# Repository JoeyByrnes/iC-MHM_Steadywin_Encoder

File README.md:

# iC-MHM_Steadywin_Encoder
PCB Design Files for iC-MHM Based Encoder PCB for the Steadywin v3 Motor

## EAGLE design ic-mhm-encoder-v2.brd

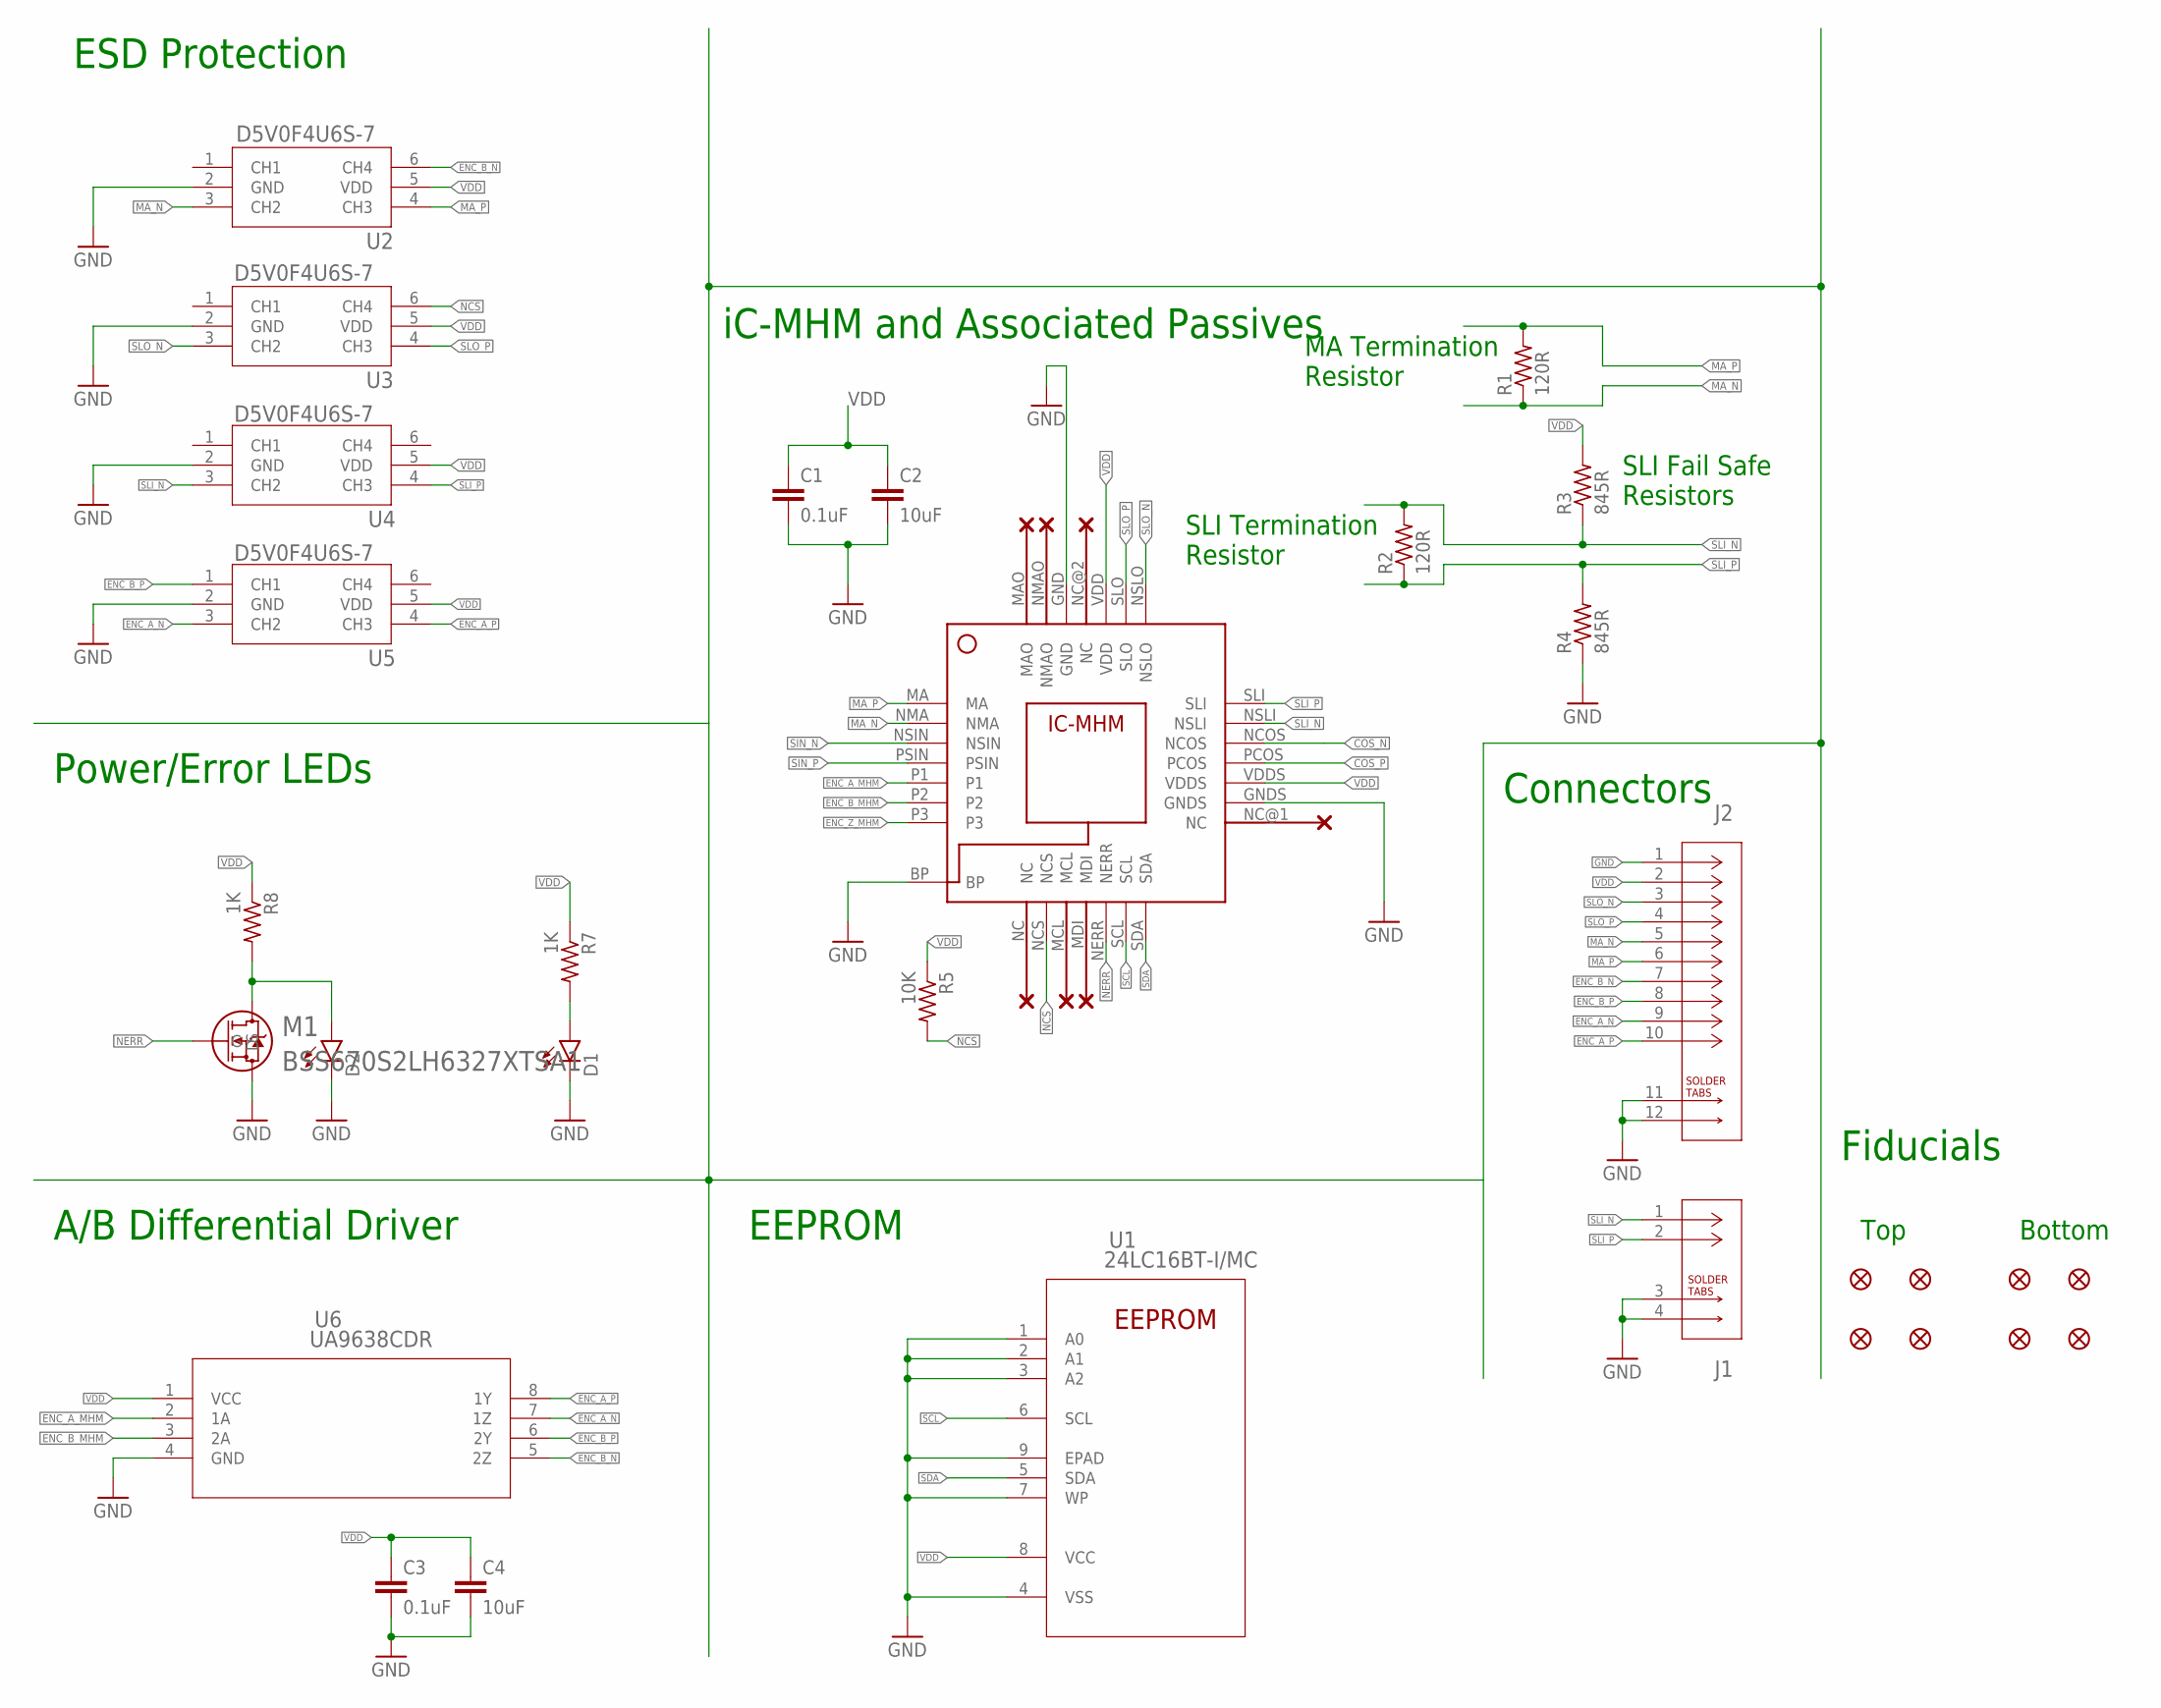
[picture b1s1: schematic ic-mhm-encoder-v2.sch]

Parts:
C1, C3: 0.1uF; C0603
C2, C4: 10uF; C0603
D1, D2: LEDSML0603; SML0603
FID1, FID2, FID3, FID4, FID5, FID6, FID7, FID8: FIDUCIAL_1MM
J1: 2023960207; CON_2023960207
J2: 2023961007; CON_2023961007
M1: BSS670S2LH6327XTSA1; PG-SOT23-3-5_INF
R1, R2: 120R; R0603
R3, R4: 845R; R0603
R5: 10K; R0603
R7, R8: 1K; R0603
U1: 24LC16BT-I/MC; DFN8_2X3MC_MCH
U2, U3, U4, U5: D5V0F4U6S-7; SOT-363_DIO
U6: UA9638CDR; D8
U$1: IC-MHM

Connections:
COS_N: U$1.NCOS
COS_P: U$1.PCOS
ENC_A_MHM: U6.2 (1A), U$1.P1
ENC_A_N: J2.9, U5.3 (CH2), U6.7 (1Z)
ENC_A_P: J2.10, U5.4 (CH3), U6.8 (1Y)
ENC_B_MHM: U6.3 (2A), U$1.P2
ENC_B_N: J2.7, U2.6 (CH4), U6.5 (2Z)
ENC_B_P: J2.8, U5.1 (CH1), U6.6 (2Y)
ENC_Z_MHM: U$1.P3
GND: C1.2, C2.2, C3.2, C4.2, D1.C, D2.C, J1.3, J1.4, J2.1, J2.11, J2.12, M1.2 (S), R4.1, U1.1 (A0), U1.2 (A1), U1.3 (A2), U1.4 (VSS), U1.7 (WP), U1.9 (EPAD), U2.2 (GND), U3.2 (GND), U4.2 (GND), U5.2 (GND), U6.4 (GND), U$1.BP, U$1.GND, U$1.GNDS
MA_N: J2.5, R1.1, U2.3 (CH2), U$1.NMA
MA_P: J2.6, R1.2, U2.4 (CH3), U$1.MA
unnamed: D1.A, R7.2
unnamed: D2.A, M1.3 (D), R8.2
NCS: R5.2, U3.6 (CH4), U$1.NCS
NERR: M1.1 (G), U$1.NERR
SCL: U1.6 (SCL), U$1.SCL
SDA: U1.5 (SDA), U$1.SDA
SIN_N: U$1.NSIN
SIN_P: U$1.PSIN
SLI_N: J1.1, R2.2, R3.1, U4.3 (CH2), U$1.NSLI
SLI_P: J1.2, R2.1, R4.2, U4.4 (CH3), U$1.SLI
SLO_N: J2.3, U3.3 (CH2), U$1.NSLO
SLO_P: J2.4, U3.4 (CH3), U$1.SLO
VDD: C1.1, C2.1, C3.1, C4.1, J2.2, R3.2, R5.1, R7.1, R8.1, U1.8 (VCC), U2.5 (VDD), U3.5 (VDD), U4.5 (VDD), U5.5 (VDD), U6.1 (VCC), U$1.VDD, U$1.VDDS

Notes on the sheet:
MA Termination Resistor
SLI Termination Resistor
SLI Fail Safe Resistors
ESD Protection
iC-MHM and Associated Passives
Fiducials
Power/Error LEDs
A/B Differential Driver
EEPROM
Connectors
Top
Bottom

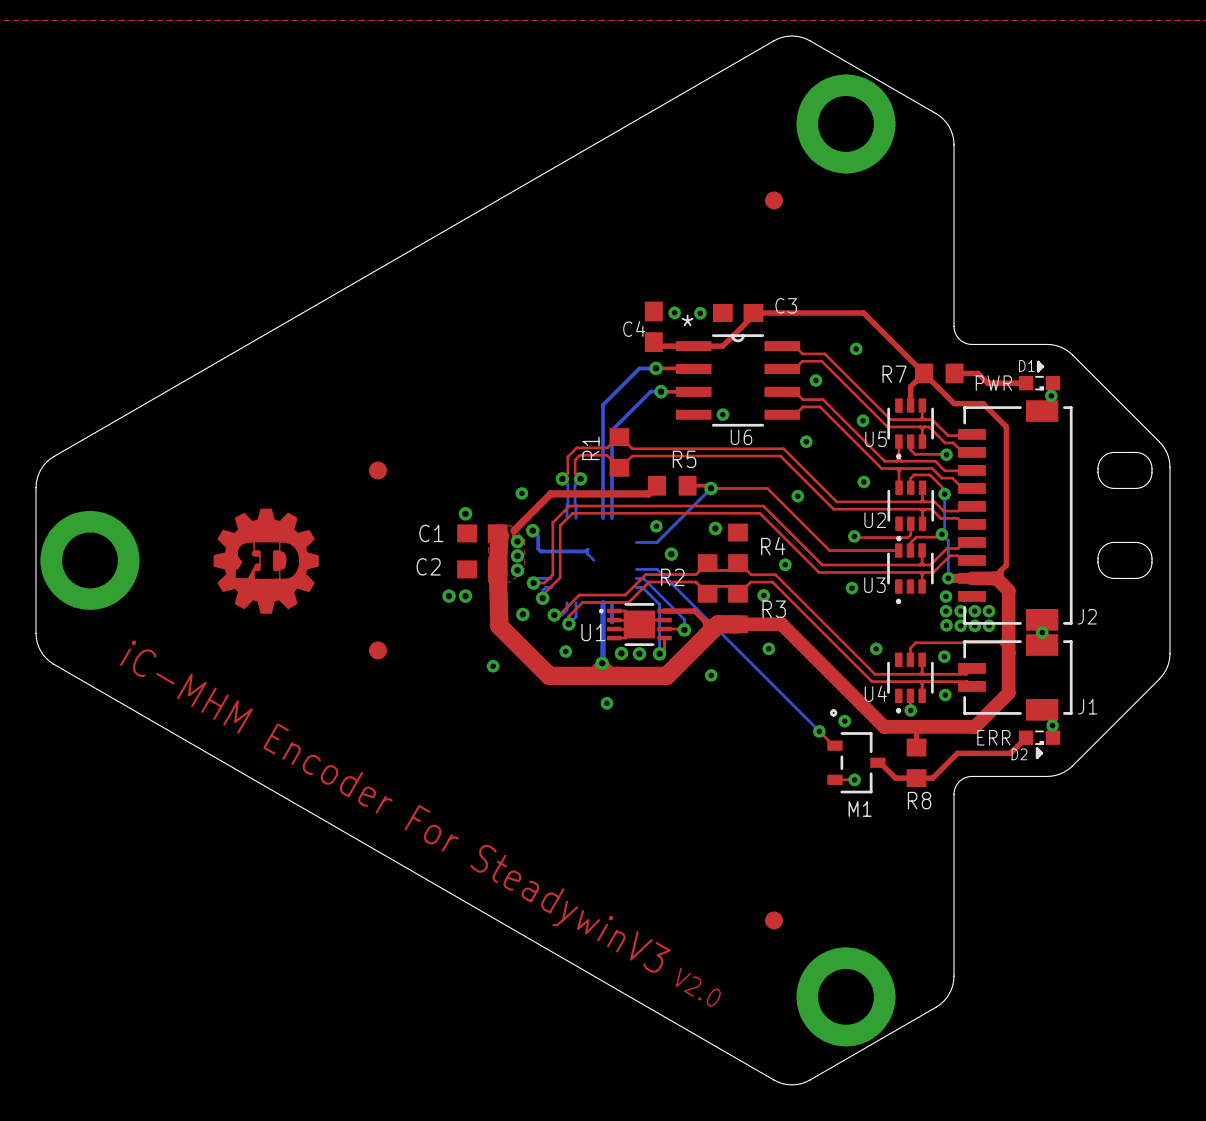
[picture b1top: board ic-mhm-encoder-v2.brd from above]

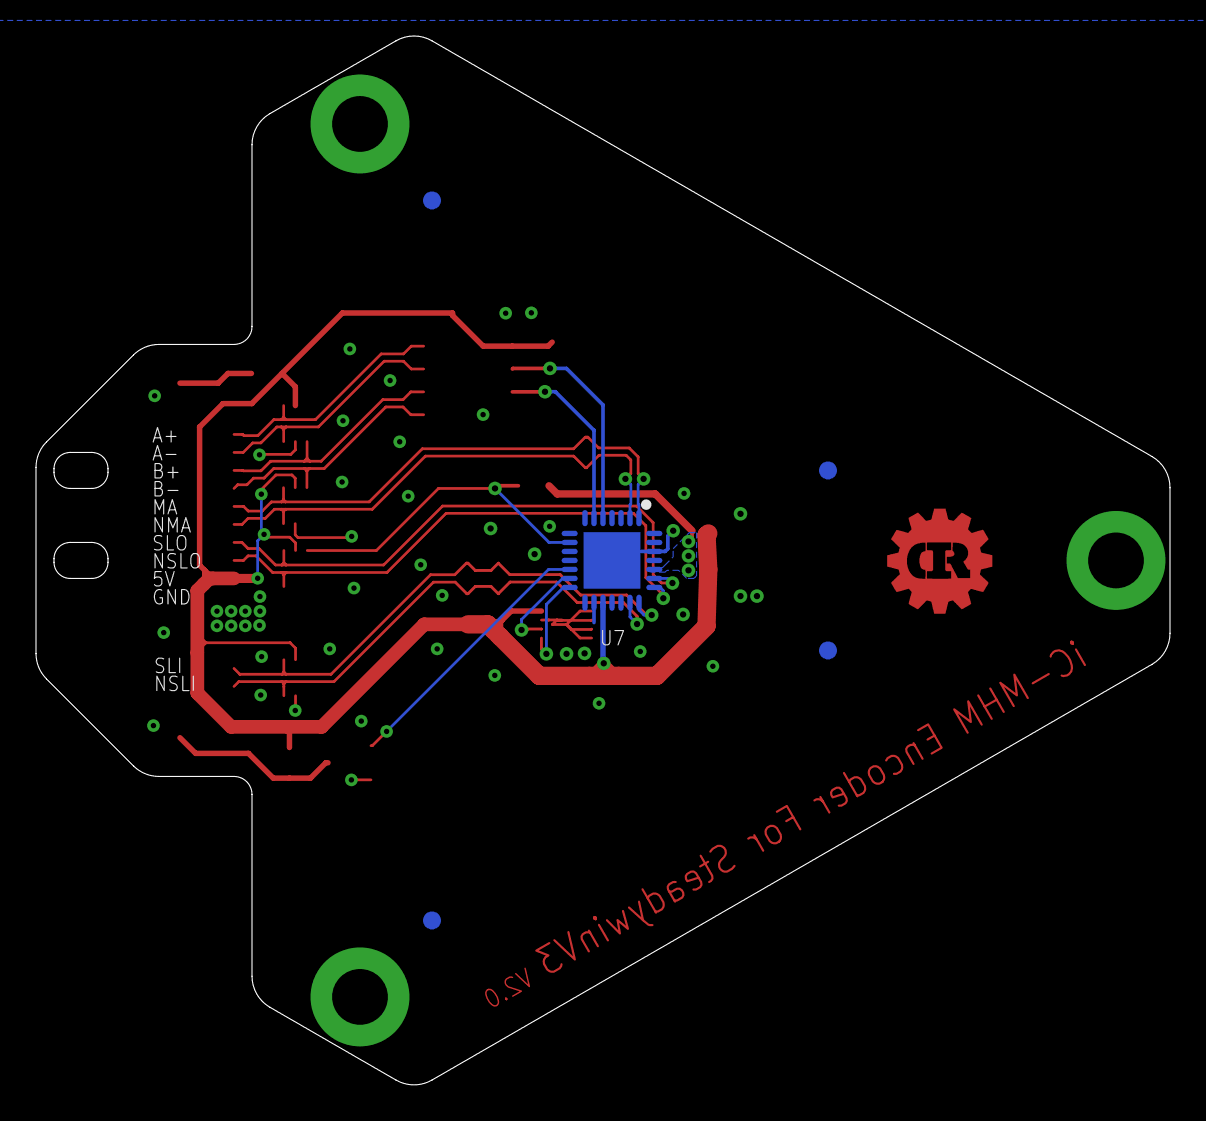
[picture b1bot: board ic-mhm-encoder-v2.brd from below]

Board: 4 copper layers, 63.0 x 58.3 mm, 31 parts (5 on the bottom side), 20 nets.

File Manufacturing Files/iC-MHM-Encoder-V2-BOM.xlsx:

Manufacturer Part Number | Manufacturer Name | Description | QTY | Digi-Key Part Number 1 | Datasheet | Reference Designator
24LC16BT-I/MC | Microchip Technology | IC EEPROM 16KBIT I2C 400KHZ 8DFN | 1 | 24LC16BT-I/MCCT-ND | https://ww1.microchip.com/downloads/en/DeviceDoc/20001703M.pdf | U1
BSS670S2LH6327XTSA1 | Infineon Technologies | MOSFET N-CH 55V 540MA SOT23-3 | 1 | BSS670S2LH6327XTSA1CT-ND | https://www.infineon.com/dgdl/BSS670S2L_Rev2.5.pdf?folderId=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 | M1
D5V0F4U6S-7 | Diodes Incorporated | TVS DIODE 5.5VWM 12VC SOT363 | 4 | 31-D5V0F4U6S-7CT-ND | https://www.diodes.com/assets/Datasheets/D5V0F4U6S.pdf | U2, U3, U4, U5
06035C104K4T4A | KYOCERA AVX | CAP CER 0.1UF 50V X7R 0603 | 2 | 478-9903-1-ND | https://datasheets.kyocera-avx.com/AutoMLCC.pdf | C1, C3
0603ZD106KAT2A | KYOCERA AVX | CAP CER 10UF 10V X5R 0603 | 2 | 478-10766-1-ND | https://datasheets.kyocera-avx.com/cx5r.pdf | C2, C4
ERJ-PA3F1200V | Panasonic Electronic Components | RES SMD 120 OHM 1% 1/3W 0603 | 2 | P120BYCT-ND | https://industrial.panasonic.com/cdbs/www-data/pdf/RDO0000/A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 | R1, R2
RE0603FRE071KL | YAGEO | RES SMD 1K OHM 1% 1/10W 0603 | 2 | 13-RE0603FRE071KLCT-ND | https://www.yageo.com/upload/media/product/productsearch/dat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 | R7, R8
ESR03EZPF1002 | Rohm Semiconductor | RES SMD 10K OHM 1% 1/4W 0603 | 1 | RHM10KADCT-ND | https://fscdn.rohm.com/en/products/databook/datasheet/passiv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 | R5
RC0603FR-07845RL | YAGEO | RES 845 OHM 1% 1/10W 0603 | 2 | 311-845HRCT-ND | https://www.yageo.com/upload/media/product/productsearch/dat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 | R3, R4
150060RS75000 | Würth Elektronik | LED RED CLEAR 0603 SMD | 1 | 732-4978-1-ND | https://www.we-online.com/katalog/datasheet/150060RS75000.pdf | D2
150060VS75000 | Würth Elektronik | LED GREEN CLEAR 0603 SMD | 1 | 732-4980-1-ND | https://www.we-online.com/katalog/datasheet/150060VS75000.pdf | D1
UA9638CDR | Texas Instruments | IC DRIVER 2/0 8SOIC | 1 | 296-15058-1-ND | https://www.ti.com/general/docs/suppproductinfo.tsp?distId=1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 | U6
2023960207 | Molex | CONN HEADER SMD R/A 2POS 1MM | 1 | WM26783CT-ND | https://www.molex.com/pdm_docs/sd/2023960207_sd.pdf | J1
2023961007 | Molex | CONN HEADER SMD R/A 10POS 1MM | 1 | WM26787CT-ND | https://www.molex.com/pdm_docs/sd/2023961007_sd.pdf | J2
iC-MHM | iC-Haus | https://www.ichaus.de/product/ic-mhm | 1 | N/A | https://www.ichaus.de/MHM_datasheet_en | U7

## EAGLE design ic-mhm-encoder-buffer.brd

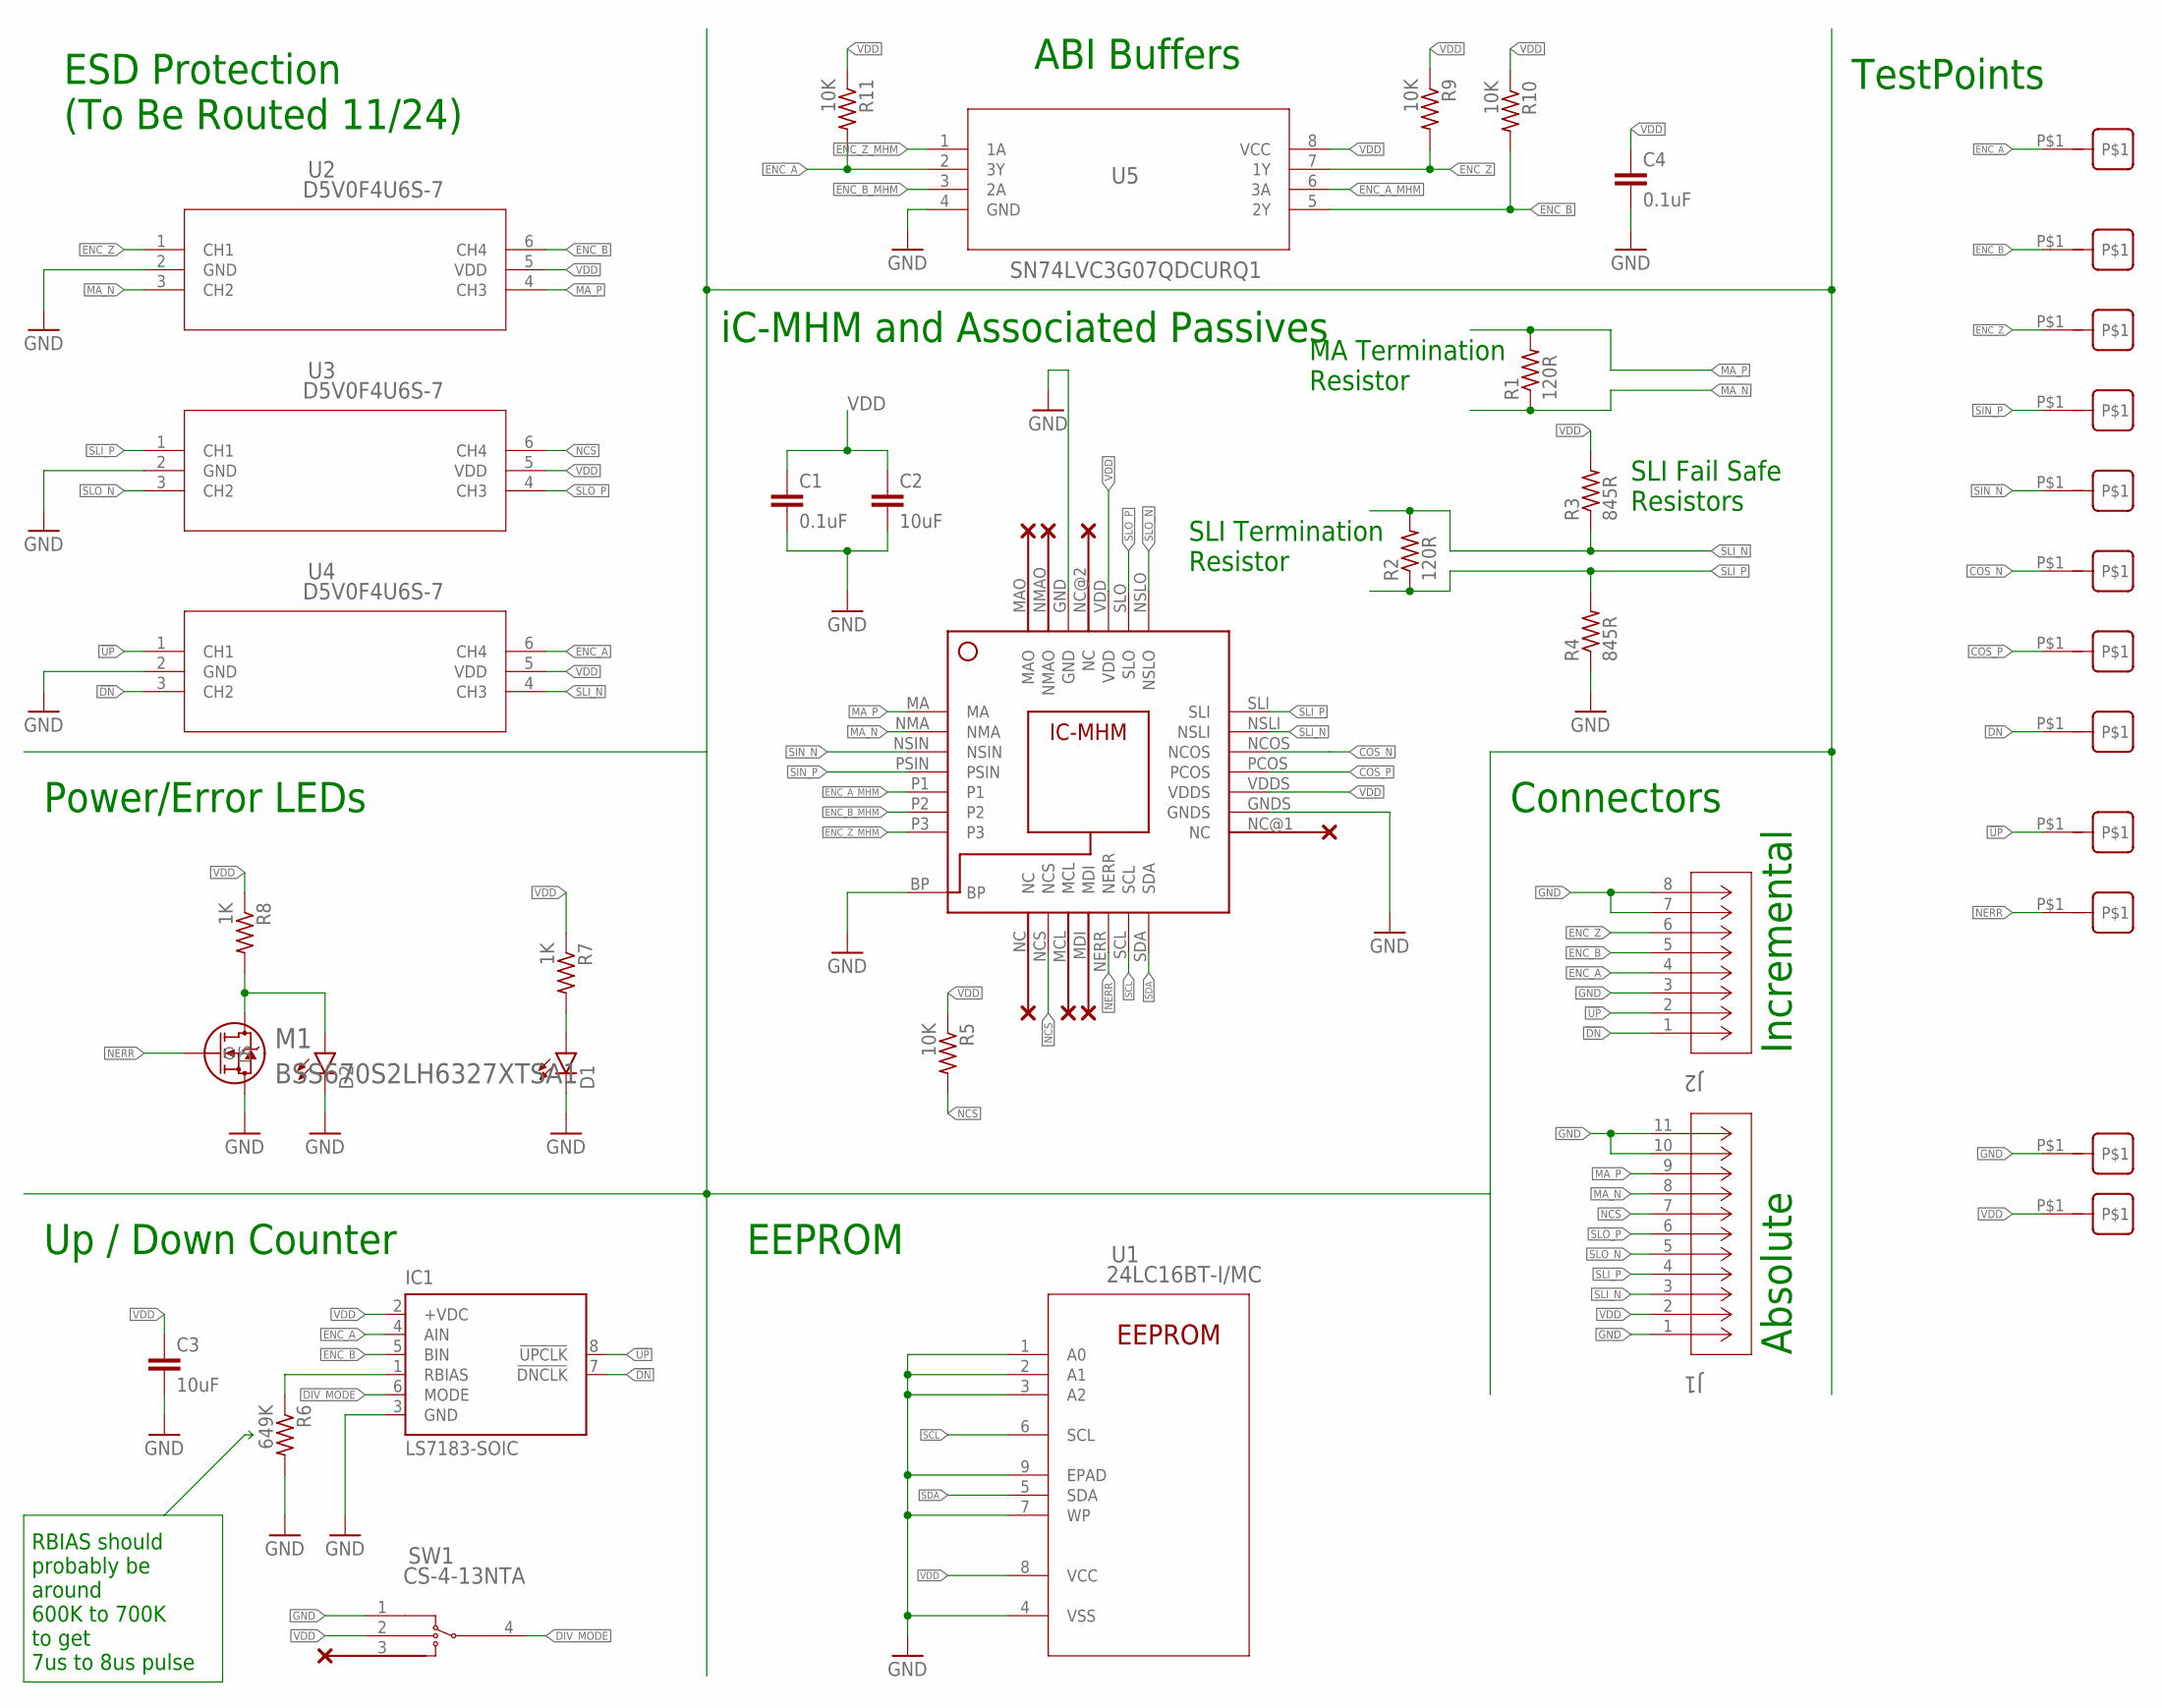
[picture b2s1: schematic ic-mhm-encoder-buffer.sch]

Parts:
C1, C4: 0.1uF; C0603
C2, C3: 10uF; C0805
D1, D2: LEDSML0603; SML0603
IC1: LS7183-SOIC; SOIC08
J1: 2023960907; CON_2023960907
J2: 2023960607; CON_2023960607
M1: BSS670S2LH6327XTSA1; PG-SOT23-3-5_INF
R1, R2: 120R; R0603
R3, R4: 845R; R0603
R5, R9, R10, R11: 10K; R0603
R6: 649K; R0603
R7, R8: 1K; R0603
SW1: CS-4-13NTA; CS-4-13NA_NDC
U1: 24LC16BT-I/MC; DFN8_2X3MC_MCH
U2, U3, U4: D5V0F4U6S-7; SOT-363_DIO
U5: SN74LVC3G07QDCURQ1; DCU8_TEX
U$1: IC-MHM
U$2, U$3, U$4, U$5, U$6, U$7, U$8, U$9, U$10, U$11, U$15, U$16: TESTPOINT_S1751-46

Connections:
!DN: IC1.7 (!DNCLK), J2.1, U4.3 (CH2), U$8.P$1
!UP: IC1.8 (!UPCLK), J2.2, U4.1 (CH1), U$9.P$1
COS_N: U$1.NCOS, U$7.P$1
COS_P: U$1.PCOS, U$11.P$1
DIV_MODE: IC1.6 (MODE), SW1.4
ENC_A: IC1.4 (AIN), J2.4, R11.2, U4.6 (CH4), U5.2 (3Y), U$2.P$1
ENC_A_MHM: U5.6 (3A), U$1.P1
ENC_B: IC1.5 (BIN), J2.5, R10.2, U2.6 (CH4), U5.5 (2Y), U$3.P$1
ENC_B_MHM: U5.3 (2A), U$1.P2
ENC_Z: J2.6, R9.2, U2.1 (CH1), U5.7 (1Y), U$4.P$1
ENC_Z_MHM: U5.1 (1A), U$1.P3
GND: C1.2, C2.2, C3.2, C4.2, D1.C, D2.C, IC1.3 (GND), J1.1, J1.10, J1.11, J2.3, J2.7, J2.8, M1.2 (S), R4.1, R6.2, SW1.1, U1.1 (A0), U1.2 (A1), U1.3 (A2), U1.4 (VSS), U1.7 (WP), U1.9 (EPAD), U2.2 (GND), U3.2 (GND), U4.2 (GND), U5.4 (GND), U$1.BP, U$1.GND, U$1.GNDS, U$15.P$1
MA_N: J1.8, R1.1, U2.3 (CH2), U$1.NMA
MA_P: J1.9, R1.2, U2.4 (CH3), U$1.MA
unnamed: IC1.1 (RBIAS), R6.1
unnamed: D1.A, R7.2
unnamed: D2.A, M1.3 (D), R8.2
NCS: J1.7, R5.2, U3.6 (CH4), U$1.NCS
NERR: M1.1 (G), U$1.NERR, U$10.P$1
SCL: U1.6 (SCL), U$1.SCL
SDA: U1.5 (SDA), U$1.SDA
SIN_N: U$1.NSIN, U$6.P$1
SIN_P: U$1.PSIN, U$5.P$1
SLI_N: J1.3, R2.2, R3.1, U4.4 (CH3), U$1.NSLI
SLI_P: J1.4, R2.1, R4.2, U3.1 (CH1), U$1.SLI
SLO_N: J1.5, U3.3 (CH2), U$1.NSLO
SLO_P: J1.6, U3.4 (CH3), U$1.SLO
VDD: C1.1, C2.1, C3.1, C4.1, IC1.2 (+VDC), J1.2, R3.2, R5.1, R7.1, R8.1, R9.1, R10.1, R11.1, SW1.2, U1.8 (VCC), U2.5 (VDD), U3.5 (VDD), U4.5 (VDD), U5.8 (VCC), U$1.VDD, U$1.VDDS, U$16.P$1

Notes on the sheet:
MA Termination Resistor
SLI Termination Resistor
SLI Fail Safe Resistors
ESD Protection (To Be Routed 11/24)
iC-MHM and Associated Passives
TestPoints
Power/Error LEDs
Up / Down Counter
EEPROM
Connectors
Absolute
Incremental
RBIAS should probably be around 600K to 700K to get 7us to 8us pulse
ABI Buffers

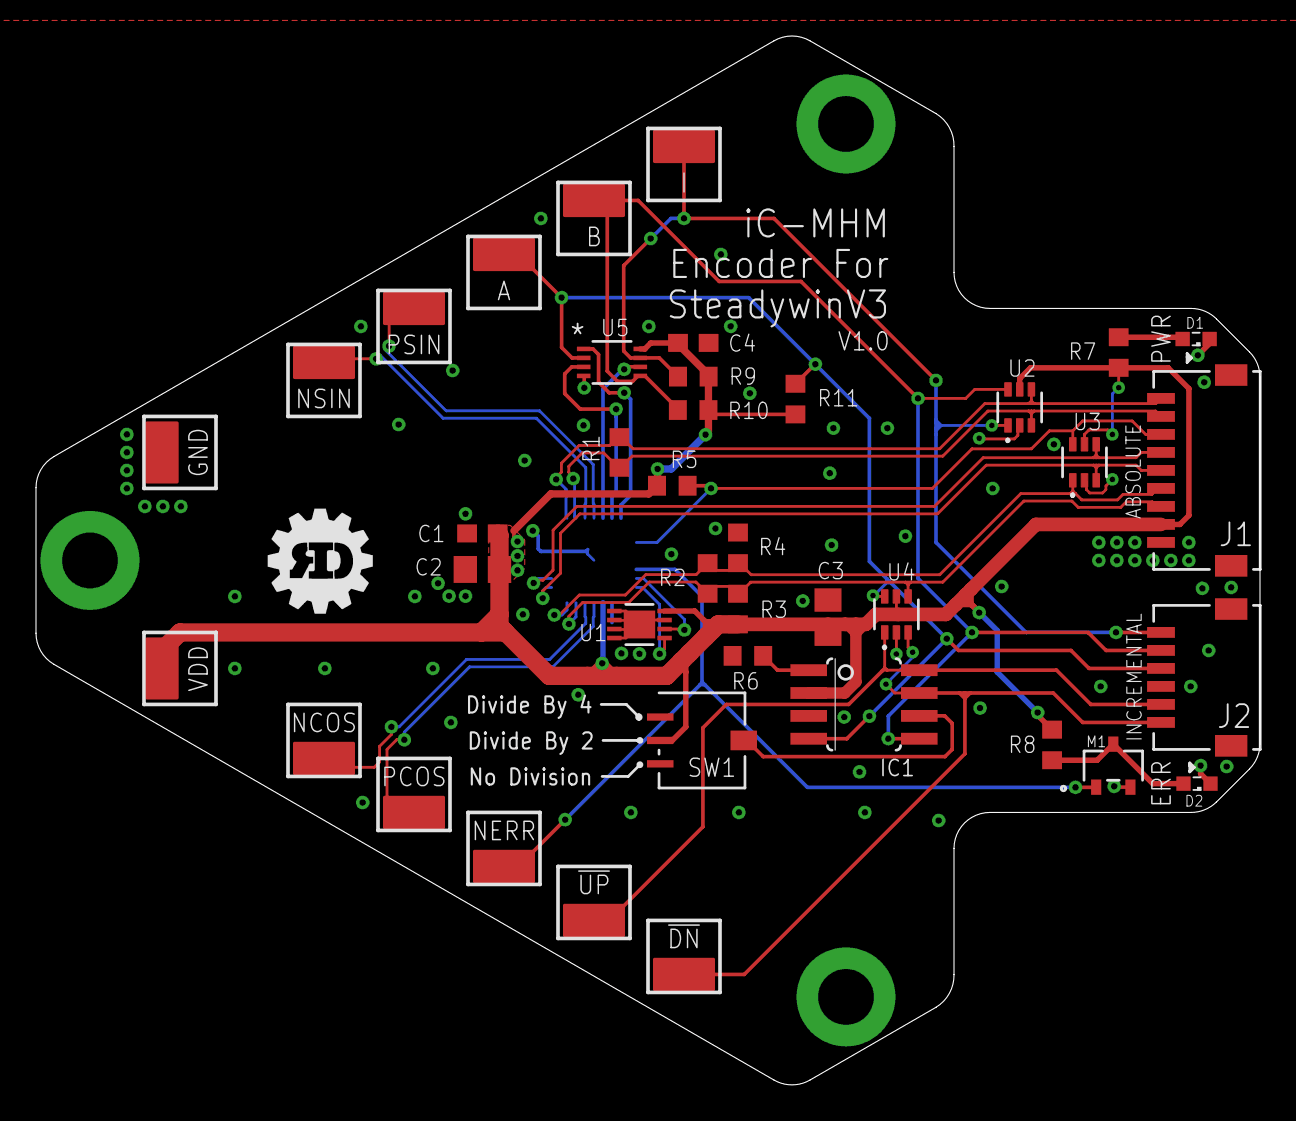
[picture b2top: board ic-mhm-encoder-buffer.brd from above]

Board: 4 copper layers, 68.0 x 58.3 mm, 40 parts (1 on the bottom side), 28 nets.

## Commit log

2021-11-24 Layout almost complete, ESD diodes needs routing, Review needed
2021-11-24 added ReadMe visuals
2021-11-24 added 3D model of Encoder
2021-11-24 added STEP model
2021-11-29 Routed ESD Diodes
2021-11-29 changed RBIAS and added note about range
2021-12-01 Added Bill of Materials
2021-12-01 Added PDF Schematic
2021-12-01 Improved GND vias
2021-12-01 Fixed/Approved all DRC Errors
2021-12-01 moved termination resistors closer to mhm
2021-12-04 added verisons with buffers on ABI
2021-12-04 Updated BOM with buffer components
2021-12-04 moved unused designs to alternate designs folder
2021-12-04 updated pdf to schematic with buffers
2021-12-04 Added GERBERs with how to order ReadME
2021-12-04 Design Ready to Order
2021-12-20 switched to 1k pullups and 0805 10uF
2022-03-25 Added config file for working BISS-C configuration
2022-05-30 visualization options added
2022-06-28 V2 encoder work in progress
2022-07-07 Finished routing of v2 pcb, ready for design review
2022-07-08 added zip tie slots
2022-07-13 updated readme in mfg folder
2022-07-13 added mfg and assembly files for v2
2022-07-13 V2 PCB Ready for Assembly Order

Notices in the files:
parts and their libraries:
COPYRIGHT: Copyright (C) 2021 Ultra Librarian. All rights reserved.
microbuilder: This work is placed in the public domain, and may be freely used for commercial and non-commercial work with the following conditions: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
COPYRIGHT: Copyright (C) 2022 Ultra Librarian. All rights reserved.
